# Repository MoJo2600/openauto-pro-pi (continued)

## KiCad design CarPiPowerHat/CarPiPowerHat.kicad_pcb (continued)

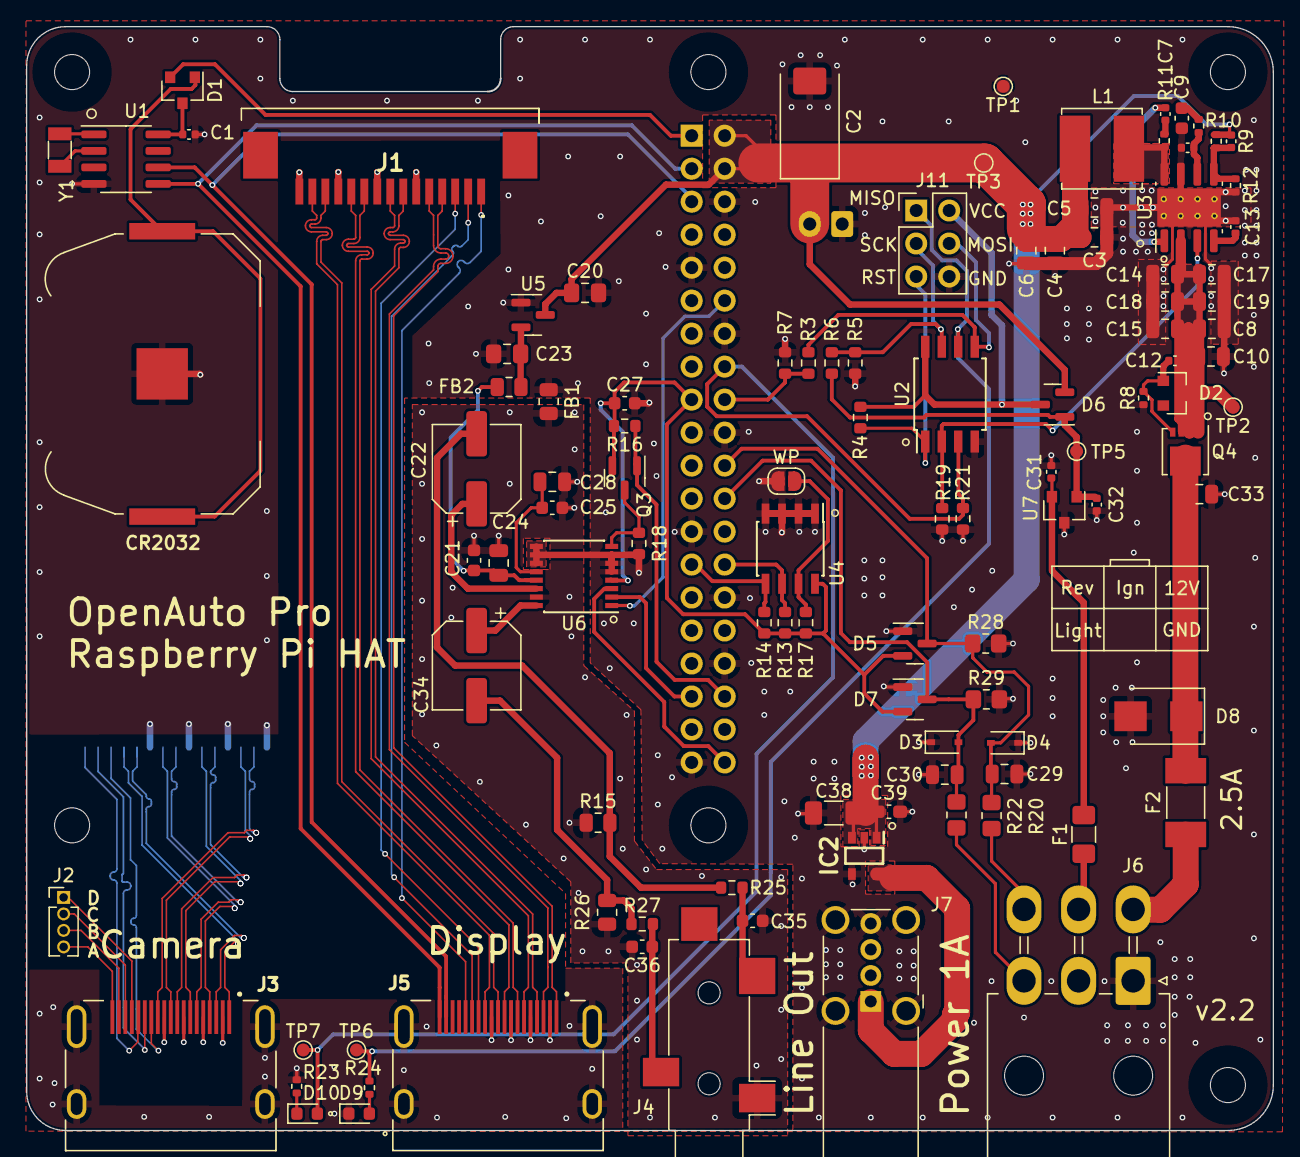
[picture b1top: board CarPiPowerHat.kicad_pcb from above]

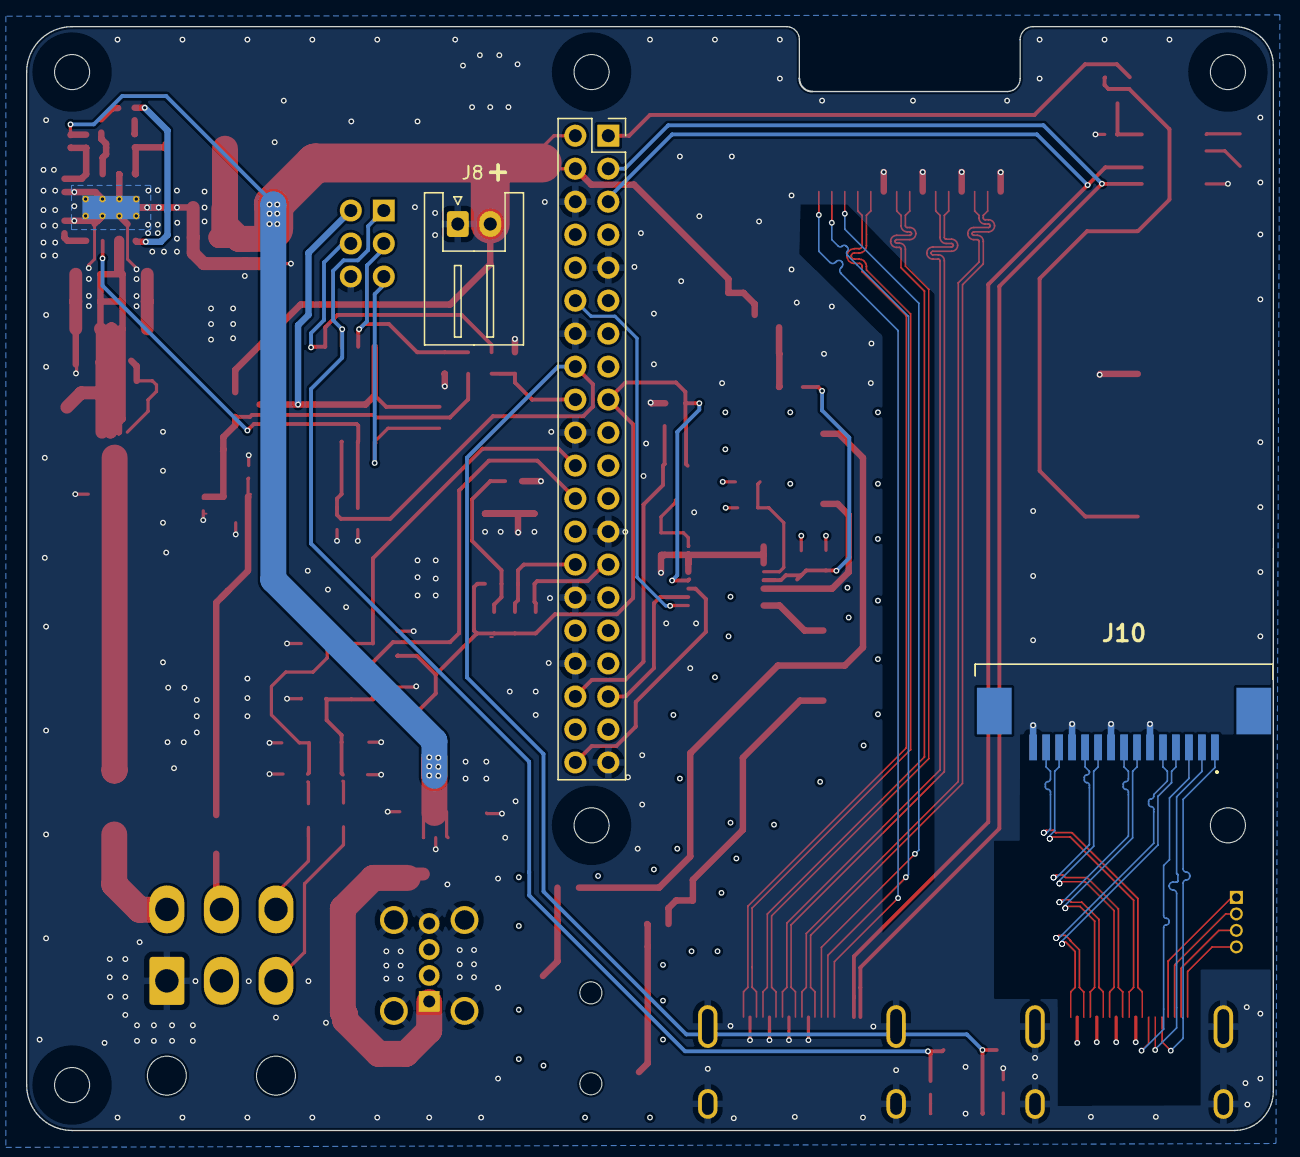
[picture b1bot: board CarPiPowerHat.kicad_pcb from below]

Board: 4 copper layers, 96.0 x 85.0 mm, 115 parts (3 on the bottom side), 82 nets.

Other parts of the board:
C30: 22nF; C_0805_2012Metric
D3: PESD12VL1BA-N; D_SOD-323
D7: BAT54S; SOT-23
J3: HDMI_A_1.4; EDAC 690-019-298-412
J10: 1-84953-5; 1849535
R22: 10k; R_0805_2012Metric_Pad1.20x1.40mm_HandSolder
R29: 1M; R_0805_2012Metric_Pad1.20x1.40mm_HandSolder

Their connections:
/+3.3v: D7.2; also elsewhere on the board
/HDMI Connector Camera/A: J3.19 (HPD/HEAC-); also elsewhere on the board
/HDMI Connector Camera/B: J3.18 (+5V); also elsewhere on the board
/HDMI Connector Camera/C: J3.17 (GND); also elsewhere on the board
/HDMI Connector Camera/CEC: J3.13 (CEC), J10.3
/HDMI Connector Camera/CK+: J3.10 (CK+), J10.13
/HDMI Connector Camera/CK-: J3.12 (CK-), J10.14
/HDMI Connector Camera/C_SCL: J3.15 (SCL), J10.1
/HDMI Connector Camera/D: J3.16 (SDA); also elsewhere on the board
/HDMI Connector Camera/D0+: J3.7 (D0+), J10.10
/HDMI Connector Camera/D0-: J3.9 (D0-), J10.11
/HDMI Connector Camera/D1+: J3.6 (D1-), J10.8
/HDMI Connector Camera/D1-: J3.4 (D1+), J10.7
/HDMI Connector Camera/D2+: J3.1 (D2+), J10.4
/HDMI Connector Camera/D2-: J3.3 (D2-), J10.5
/HDMI Connector Camera/UTILITY/HEAC+: J3.14 (UTILITY/HEAC+), J10.2
/Light Input/OUT: C30.1, D3.2 (A2), D7.3, R22.1, R29.1; also elsewhere on the board
CAR_LIGHT: R22.2; also elsewhere on the board
GND: C30.2, D3.1 (A1), D7.1, J3.2 (D2S), J3.5 (D1S), J3.8 (D0S), J3.11 (CKS), J3.SH1 (SH), J3.SH2 (SH), J3.SH3 (SH), J3.SH4 (SH), J10.6, J10.9, J10.12, J10.15, R29.2; also elsewhere on the board

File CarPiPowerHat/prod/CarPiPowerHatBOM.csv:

Comment,Designator,Footprint,LCSC
"Battery_Cell","BT1","Battery:BatteryHolder_Keystone_3034_1x20mm",""
"nf","C11,C16","Capacitor_SMD:C_0402_1005Metric",""
"100uF","C2","Capacitor_Tantalum_SMD:CP_EIA-7343-31_Kemet-D",""
"1uF","C20,C23","Capacitor_SMD:C_0805_2012Metric_Pad1.18x1.45mm_HandSolder","C28323"
"0.1uF","C21,C25,C27","Capacitor_SMD:C_0603_1608Metric","C14663"
"47uF","C22,C34","Capacitor_SMD:CP_Elec_6.3x7.7","C164078"
"22nF","C29,C30","Capacitor_SMD:C_0805_2012Metric","C1729"
"10uF","C3,C4,C5,C6,C24,C28","Capacitor_SMD:C_0805_2012Metric","C15850"
"100n 100v","C33","Capacitor_SMD:C_0805_2012Metric","C28233"
"0.01uF","C35,C36","Capacitor_SMD:C_0603_1608Metric","C57112"
"100uF","C38","Capacitor_SMD:C_1206_3216Metric_Pad1.33x1.80mm_HandSolder","C15008"
"1uF","C39","Capacitor_SMD:C_0603_1608Metric_Pad1.08x0.95mm_HandSolder","C15849"
"100n 16v","C1,C7,C12,C13,C31,C32","Capacitor_SMD:C_0402_1005Metric","C1525"
"10uF 35v","C8,C10,C14,C15,C17,C18,C19","Capacitor_SMD:C_0805_2012Metric","C440198"
"1.2nF","C9","Capacitor_SMD:C_0603_1608Metric","C30615"
"LED Green","D10","LED_SMD:LED_0603_1608Metric","C72043"
"MMBZ5242BLT3G","D2","Diode_SMD:D_SOT-23_ANK","C268585"
"PESD12VL1BA-N","D3,D4","Diode_SMD:D_SOD-323","C314261"
"BAT54S","D5,D7","Package_TO_SOT_SMD:SOT-23","C408389"
"BAT54C-7-F","D1,D6","Package_TO_SOT_SMD:SOT-23","C37704"
"SMBJ33A","D8","Diode_SMD:D_SMB","C353366"
"LED Blue","D9","LED_SMD:LED_0603_1608Metric","C72041"
"Fuse","F1","Fuse:Fuse_1206_3216Metric_Pad1.42x1.75mm_HandSolder","C206984"
"Fuse","F2","Fuse:Fuse_Littelfuse-NANO2-451_453",""
"Ferrite","FB1,FB2","Resistor_SMD:R_0805_2012Metric","C1017"
"3mm_Mounting_Hole","H1,H2,H3,H4,H5,H6","MountingHole:MountingHole_2.7mm_M2.5",""
"BD2226G-TR","IC2","SamacSys_Parts:SOT95P280X125-5N","C308587"
"1-84953-5","J1,J10","SamacSys_Parts:1849535",""
"Conn_01x06_Male","J11","Connector_PinHeader_2.54mm:PinHeader_2x03_P2.54mm_Vertical",""
"Conn_01x04","J2","Connector_PinHeader_2.00mm:PinHeader_1x04_P2.00mm_Vertical",""
"HDMI_A_1.4","J3,J5","project_footprints:EDAC 690-019-298-412",""
"AudioJack2_Ground","J4","Connector_Audio:Jack_3.5mm_CUI_SJ-3524-SMT_Horizontal",""
"Conn_02x03_Counter_Clockwise","J6","Connector_Molex:Molex_Mini-Fit_Jr_5569-06A2_2x03_P4.20mm_Horizontal",""
"USB_A","J7","Connector_USB:USB_A_Wuerth_614004134726_Horizontal",""
"Conn_01x02_Male","J8","Connector_JST:JST_XH_S2B-XH-A_1x02_P2.50mm_Horizontal",""
"40HAT","J9","Connector_PinSocket_2.54mm:PinSocket_2x20_P2.54mm_Vertical",""
"SolderJumper_2_Open","JP1","Jumper:SolderJumper-2_P1.3mm_Open_RoundedPad1.0x1.5mm",""
"SRN6045TA-3R3Y","L1","Inductor_SMD:L_Bourns_SRN6045TA",""
"DMG2305","Q3","Package_TO_SOT_SMD:SOT-23","C144153"
"DMP3013SFV-7","Q4","Package_SON:Diodes_PowerDI3333-8","C264098"
"20K 1%","R10","Resistor_SMD:R_0402_1005Metric","C25765"
"10R","R11","Resistor_SMD:R_0402_1005Metric","C25077"
"2.2K 1%","R12","Resistor_SMD:R_0402_1005Metric","C25879"
"3.9K","R13,R14","Resistor_SMD:R_0603_1608Metric","C23018"
"220k","R15,R26","Resistor_SMD:R_0805_2012Metric","C17521"
"10K","R16,R17,R18","Resistor_SMD:R_0603_1608Metric","C25804"
"10k","R20,R22","Resistor_SMD:R_0805_2012Metric_Pad1.20x1.40mm_HandSolder","C17414"
"200 1%","R23,R24","Resistor_SMD:R_0402_1005Metric","C25087"
"100","R25,R27","Resistor_SMD:R_0603_1608Metric","C22775"
"1M","R28,R29","Resistor_SMD:R_0805_2012Metric_Pad1.20x1.40mm_HandSolder","C17514"
"10K 1%","R3,R4,R5,R7,R19,R21","Resistor_SMD:R_0603_1608Metric","C25804"
"3.3K 1%","R6","Resistor_SMD:R_0603_1608Metric","C22978"
"12K 1%","R8,R9","Resistor_SMD:R_0402_1005Metric","C25752"
"TestPoint","TP1,TP2,TP3,TP5,TP6,TP7","TestPoint:TestPoint_Pad_D1.0mm",""
"PCF85063AT/AAZ","U1","Package_SO:SOIC-8_3.9x4.9mm_P1.27mm","C7440"
"ATtiny45V-20SU","U2","Package_SO:SOIC-8W_5.3x5.3mm_P1.27mm","C62689"
"AP64501SP-13","U3","Package_SO:SOIC-8-1EP_3.9x4.9mm_P1.27mm_EP2.95x4.9mm_Mask2.71x3.4mm_ThermalVias","C2071517"
"CAT24C32","U4","Package_SOIC:SOIC-8_3.9x4.9mm_P1.27mm","C81193"
"XC6206P332MR","U5","Package_TO_SOT_SMD:SOT-23","C5446"
"UDA1334ATS","U6","Package_SO:SSOP-16_4.4x5.2mm_P0.65mm","C494494"
"LM3480-5.0","U7","Package_TO_SOT_SMD:SOT-23","C129960"
"FC-12M32.768KHZ7PF20PPM","Y1","Crystal:Crystal_SMD_3215-2Pin_3.2x1.5mm","C99009"

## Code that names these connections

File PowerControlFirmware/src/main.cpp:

#include <Arduino.h>
#include <avr/io.h>
#include <util/delay.h>
#include <Bounce2.h>

#define PIN_LED PB1                                                            // Pin to LED
#define PIN_POWER_CNTRL PB3                                                    // Pin to enable / disable power to Pi
#define PIN_IGN_SENSE PB2                                                      // Pin to sense ignition
#define PIN_PI_IN PB4                                                          // Pin from Pi to tell it is up and running
#define PIN_PI_OUT PB0                                                         // Pin to Pi to tell it to shut down
#define PULSE_DURATION_SLOW 150
#define PULSE_DURATION_FAST 30
#define PULSE_DURATION_SUPER_FAST 20
#define WAITTIME_FOR_PI_TO_RESPOND 6000
#define FINAL_WAIT_TIME 500

enum State {
  WAIT_FOR_PI_BOOT,
  RUNNING,
  WAIT_FOR_PI_SHUTDOWN,
  WAIT_FOR_PI_COME_BACK,
  SHUTDOWN,
  KILL,
};

State g_currentState = WAIT_FOR_PI_BOOT;
unsigned long g_eventStartMillis = 0L;
Bounce g_ignSense = Bounce();                                                  // Instantiate a Bounce object

// pin states
int g_ignitionOn = true;
int g_piOn = false;

void pulseLed(int speed) {
  analogWrite(PIN_LED, sin( 2 * PI / speed * (millis() - g_eventStartMillis) + 3 * PI / 2) * 128 + 128);
}

void setup() {
  pinMode(PIN_PI_IN, INPUT);
  pinMode(PIN_LED, OUTPUT);

  pinMode(PIN_POWER_CNTRL, OUTPUT);
  digitalWrite(PIN_POWER_CNTRL, 1);

  pinMode(PIN_PI_OUT, OUTPUT);
  digitalWrite(PIN_PI_OUT, 0);

  g_ignSense.attach(PIN_IGN_SENSE, INPUT);                                     // Attach the debouncer to a pin with INPUT_PULLUP mode
  g_ignSense.interval(150);                                                    // Use a debounce interval of 150 milliseconds
}

void switchState(State newState) {
  g_eventStartMillis = millis();                                               // Reset timeout timer
  g_currentState = newState;                                                   // Set new state
}

void loop() {
  if (g_ignSense.changed()) {                                                  // Get current pin states
    g_ignitionOn = g_ignSense.read();
  }
  g_piOn = digitalRead(PIN_PI_IN);

  switch(g_currentState) {
    case WAIT_FOR_PI_BOOT:
      pulseLed(PULSE_DURATION_SLOW);

      if (g_piOn) {                                                             // Pi signals it has booted
        switchState(RUNNING);
        return;
      }

      if(millis() - g_eventStartMillis > WAITTIME_FOR_PI_TO_RESPOND) {          // Timeout Pi did not shut down in time, cut power anyways
        switchState(SHUTDOWN);
        return;
      }

      break;
    case RUNNING:
      analogWrite(PIN_LED, 255);

      if (g_ignitionOn == false) {                                              // Ignition is switched off shutdown pi
        digitalWrite(PIN_PI_OUT, 1);                                            // Tell pi to shut down
        switchState(WAIT_FOR_PI_SHUTDOWN);
        return;
      }

      if (g_piOn == false) {                                                    // Pi was switched off, but ignition is still on
        switchState(WAIT_FOR_PI_COME_BACK);
        return;
      }

      break;
    case WAIT_FOR_PI_COME_BACK:                                                 // Ignition is on, but pi shut down - maybe a reboot?
      pulseLed(PULSE_DURATION_SUPER_FAST);

      if(g_piOn) {                                                              // Pi did come back online back to running
        switchState(RUNNING);
        return;
      }

      if(millis() - g_eventStartMillis > WAITTIME_FOR_PI_TO_RESPOND) {         // Timeout Pi did not come back, cut power
        switchState(SHUTDOWN);
        return;
      }

      break;
    case WAIT_FOR_PI_SHUTDOWN:                                                  // We told the pi to shut down, now we wait for shutdown
      pulseLed(PULSE_DURATION_FAST);

      if (g_piOn == false) {                                                    // Pi did shut down, cut power
        switchState(SHUTDOWN);
        return;
      }

      if(millis() - g_eventStartMillis > WAITTIME_FOR_PI_TO_RESPOND) {         // Timeout Pi did not shut down in time, cut power anyways
        switchState(SHUTDOWN);
        return;
      }

      break;
    case SHUTDOWN:
      analogWrite(PIN_LED, 25);

      if(millis() - g_eventStartMillis > FINAL_WAIT_TIME) {                    // Final wait time to make sure everything shut down
        switchState(KILL);
        return;
      }

      break;
    case KILL:
      digitalWrite(PIN_LED, 0);
      digitalWrite(PIN_POWER_CNTRL, 0);                                        // Shut down the power circuit

      // Usually shutting down the power circuit will shut down the attiny as well and the program ends here
      // It might happen, that the user restarts the engine during this time. If so, we want to
      // enable the power circuitry again after a clean shutdown
      delay(100);
      if (g_ignitionOn == true) {
        digitalWrite(PIN_POWER_CNTRL, 1);                                    // Enable the power circuit
        digitalWrite(PIN_PI_OUT, 0);
        switchState(WAIT_FOR_PI_BOOT);
      }

      break;
  }
  g_ignSense.update();                                                         // Update the Bounce instance
}

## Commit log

2021-03-07 added jtag
2021-03-17 Added first firmware version
2021-03-18 added connectors
2021-03-20 Finished implementation
2021-03-20 documentation draft
2021-03-25 doing some traces
2021-04-01 Everything routed, DRC ok
2021-04-01 Cleanup
2021-04-02 Finalizing
2021-04-10 Repositioning of connectors
2021-06-24 updated layout
2021-07-19 Create LICENSE
2021-07-19 first version of readme
2021-07-19 added some more documentation
2021-07-30 Removed TVS diodes for now, fixed DRC issues
2021-08-23 Finished Layout
2021-08-25 Added part numbers
    * Selected parts from lcsc
    * Checked footprints
2021-09-16 try to fix error in control software
2021-10-01 Fixed some bugs, not done yet
2021-10-01 removed unnecessary reverse polarity protection
2021-10-02 Some rerouting
2021-10-03 Finalized 2.2
2021-10-04 Finalizing, checking parts
    Might be ready for production
2021-11-04 Working power control firmware
2021-11-10 Start setup documentation
2021-11-23 Moved HDMI ports
    The HDMI ports were offset by 1-2 mm
2022-01-29 Some bugfixing, added cam.py script
2022-02-04 Updated schematic
2022-10-13 fix: fixed some minor inconveniences
2023-02-16 feat: advanced backlight brightness control
2023-02-20 feat: Update Brightness script
2023-03-17 chore(brightness_script): optimized deamon start / stop
2023-03-29 chore: Updated documentation
2023-03-29 fix: Update brightness service fix: Update rearcamera requirements.txt
